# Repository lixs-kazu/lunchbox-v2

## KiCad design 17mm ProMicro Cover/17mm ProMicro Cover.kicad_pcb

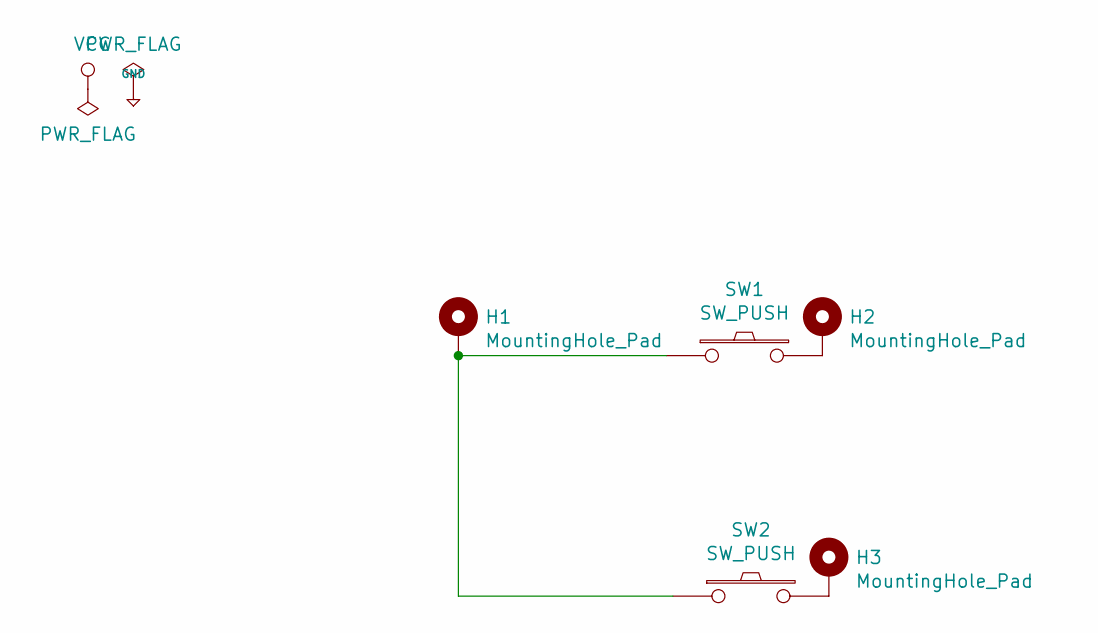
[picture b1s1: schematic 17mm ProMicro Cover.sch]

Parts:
H1, H2, H3: MountingHole_Pad; MountingHole_2.2mm_M2_DIN965_Pad
SW1, SW2: SW_PUSH; MX_PG1350_FLIP_HOLES

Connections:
unnamed: H1.1, SW1.1, SW2.1
unnamed: H2.1, SW1.2
unnamed: H3.1, SW2.2

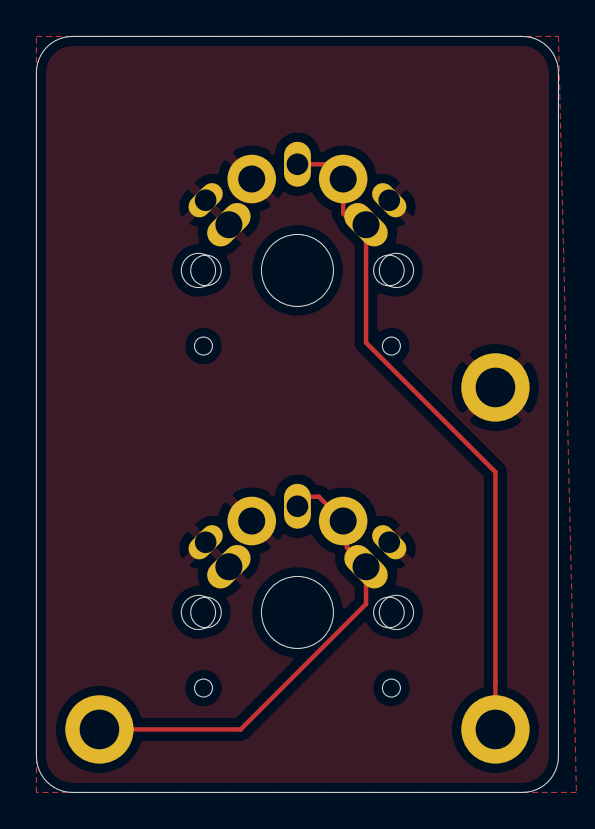
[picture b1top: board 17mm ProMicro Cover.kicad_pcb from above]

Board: 2 copper layers, 29.0 x 42.0 mm, 5 parts (0 on the bottom side), 3 nets.

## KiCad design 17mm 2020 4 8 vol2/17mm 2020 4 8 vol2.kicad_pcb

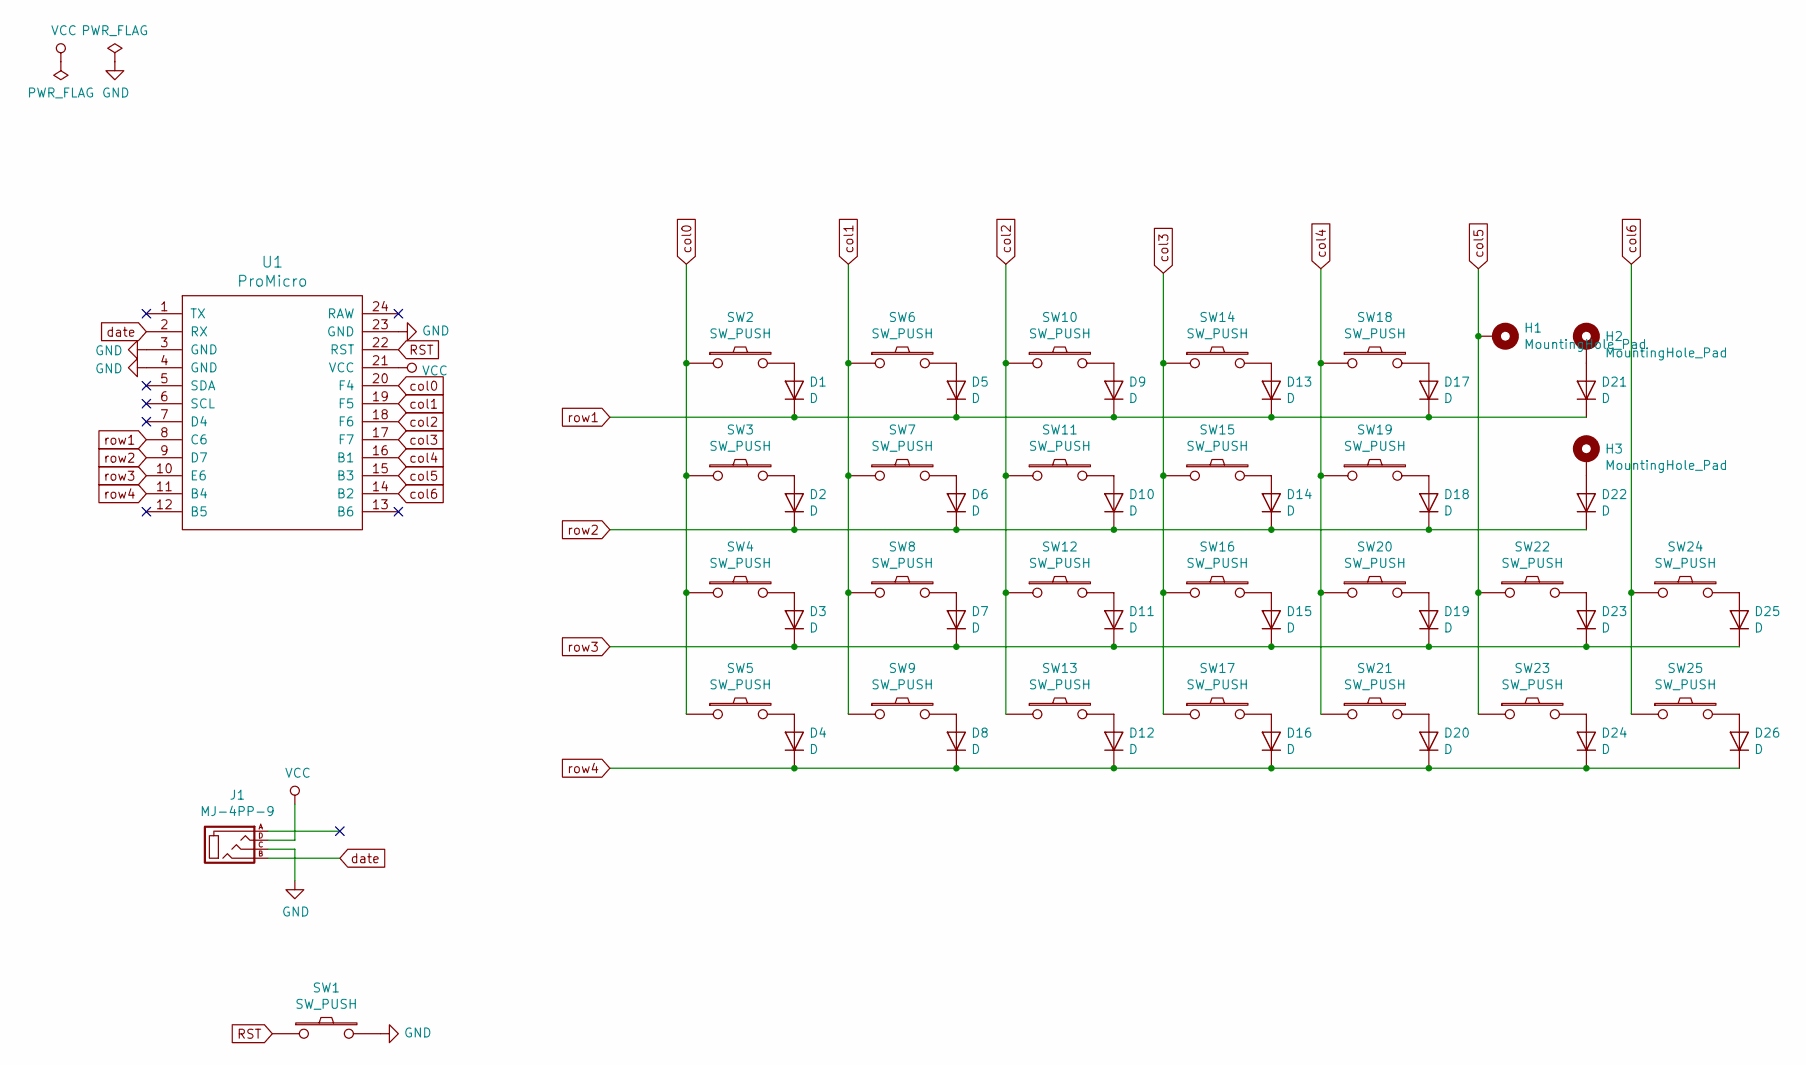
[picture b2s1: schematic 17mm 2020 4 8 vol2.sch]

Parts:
D1, D2, D3, D4, D5, D6, D7, D8, D9, D10, D11, D12, D13, D14, D15, D16, D17, D18, D19, D20, D21, D22, D23, D24, D25, D26: D; D3_SMD
H1, H2, H3: MountingHole_Pad; MountingHole_2.2mm_M2_Pad
J1: MJ-4PP-9
SW1, SW24, SW25: SW_PUSH; ResetSW
SW2, SW3, SW4, SW5, SW6, SW7, SW8, SW9, SW10, SW11, SW12, SW13, SW14, SW15, SW16, SW17, SW18, SW19, SW20, SW21, SW22, SW23: SW_PUSH; CherryMX_Choc_Hotswap
U1: ProMicro; ProMicro_v2

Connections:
GND: J1.C, SW1.2, U1.3 (GND), U1.4 (GND), U1.23 (GND)
unnamed: D1.2 (A), SW2.2
unnamed: D2.2 (A), SW3.2
unnamed: D3.2 (A), SW4.2
unnamed: D4.2 (A), SW5.2
unnamed: D5.2 (A), SW6.2
unnamed: D6.2 (A), SW7.2
unnamed: D7.2 (A), SW8.2
unnamed: D8.2 (A), SW9.2
unnamed: D9.2 (A), SW10.2
unnamed: D10.2 (A), SW11.2
unnamed: D11.2 (A), SW12.2
unnamed: D12.2 (A), SW13.2
unnamed: D13.2 (A), SW14.2
unnamed: D14.2 (A), SW15.2
unnamed: D15.2 (A), SW16.2
unnamed: D16.2 (A), SW17.2
unnamed: D17.2 (A), SW18.2
unnamed: D18.2 (A), SW19.2
unnamed: D19.2 (A), SW20.2
unnamed: D20.2 (A), SW21.2
unnamed: D21.2 (A), H2.1
unnamed: D22.2 (A), H3.1
unnamed: D23.2 (A), SW22.2
unnamed: D24.2 (A), SW23.2
unnamed: D25.2 (A), SW24.2
unnamed: D26.2 (A), SW25.2
RST: SW1.1, U1.22 (RST)
VCC: J1.D, U1.21 (VCC)
col0: SW2.1, SW3.1, SW4.1, SW5.1, U1.20 (F4)
col1: SW6.1, SW7.1, SW8.1, SW9.1, U1.19 (F5)
col2: SW10.1, SW11.1, SW12.1, SW13.1, U1.18 (F6)
col3: SW14.1, SW15.1, SW16.1, SW17.1, U1.17 (F7)
col4: SW18.1, SW19.1, SW20.1, SW21.1, U1.16 (B1)
col5: H1.1, SW22.1, SW23.1, U1.15 (B3)
col6: SW24.1, SW25.1, U1.14 (B2)
date: J1.B, U1.2 (RX)
row1: D1.1 (K), D5.1 (K), D9.1 (K), D13.1 (K), D17.1 (K), D21.1 (K), U1.8 (C6)
row2: D2.1 (K), D6.1 (K), D10.1 (K), D14.1 (K), D18.1 (K), D22.1 (K), U1.9 (D7)
row3: D3.1 (K), D7.1 (K), D11.1 (K), D15.1 (K), D19.1 (K), D23.1 (K), D25.1 (K), U1.10 (E6)
row4: D4.1 (K), D8.1 (K), D12.1 (K), D16.1 (K), D20.1 (K), D24.1 (K), D26.1 (K), U1.11 (B4)

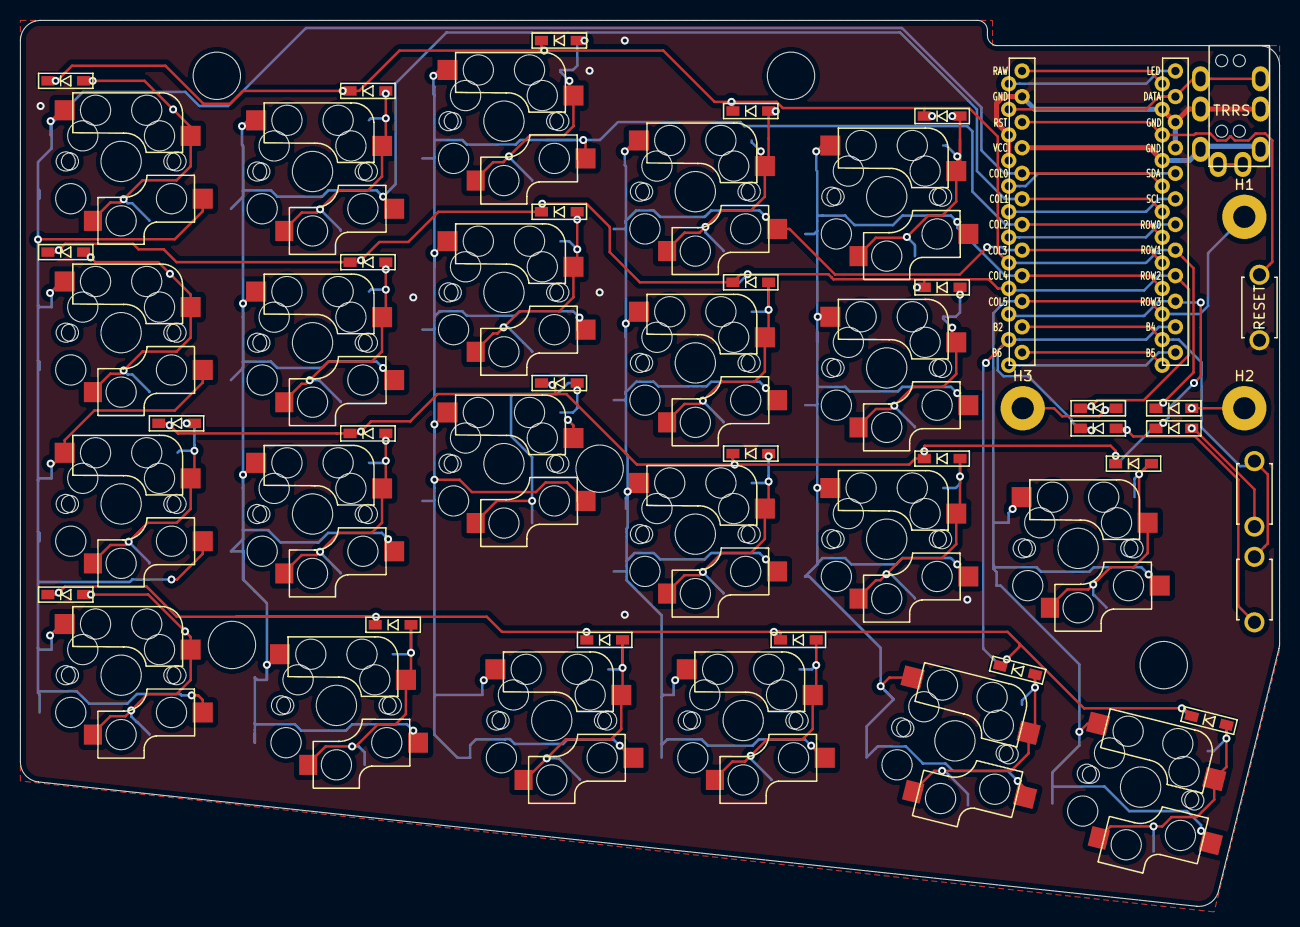
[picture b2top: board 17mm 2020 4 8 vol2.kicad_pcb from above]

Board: 2 copper layers, 125.0 x 88.0 mm, 61 parts (0 on the bottom side), 41 nets.

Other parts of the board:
HOLE_3M, HOLE_3M#2, HOLE_3M#3, HOLE_3M#4, HOLE_3M#5: VAL**; HOLE_M2_TH

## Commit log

2020-05-07 Create PCB
